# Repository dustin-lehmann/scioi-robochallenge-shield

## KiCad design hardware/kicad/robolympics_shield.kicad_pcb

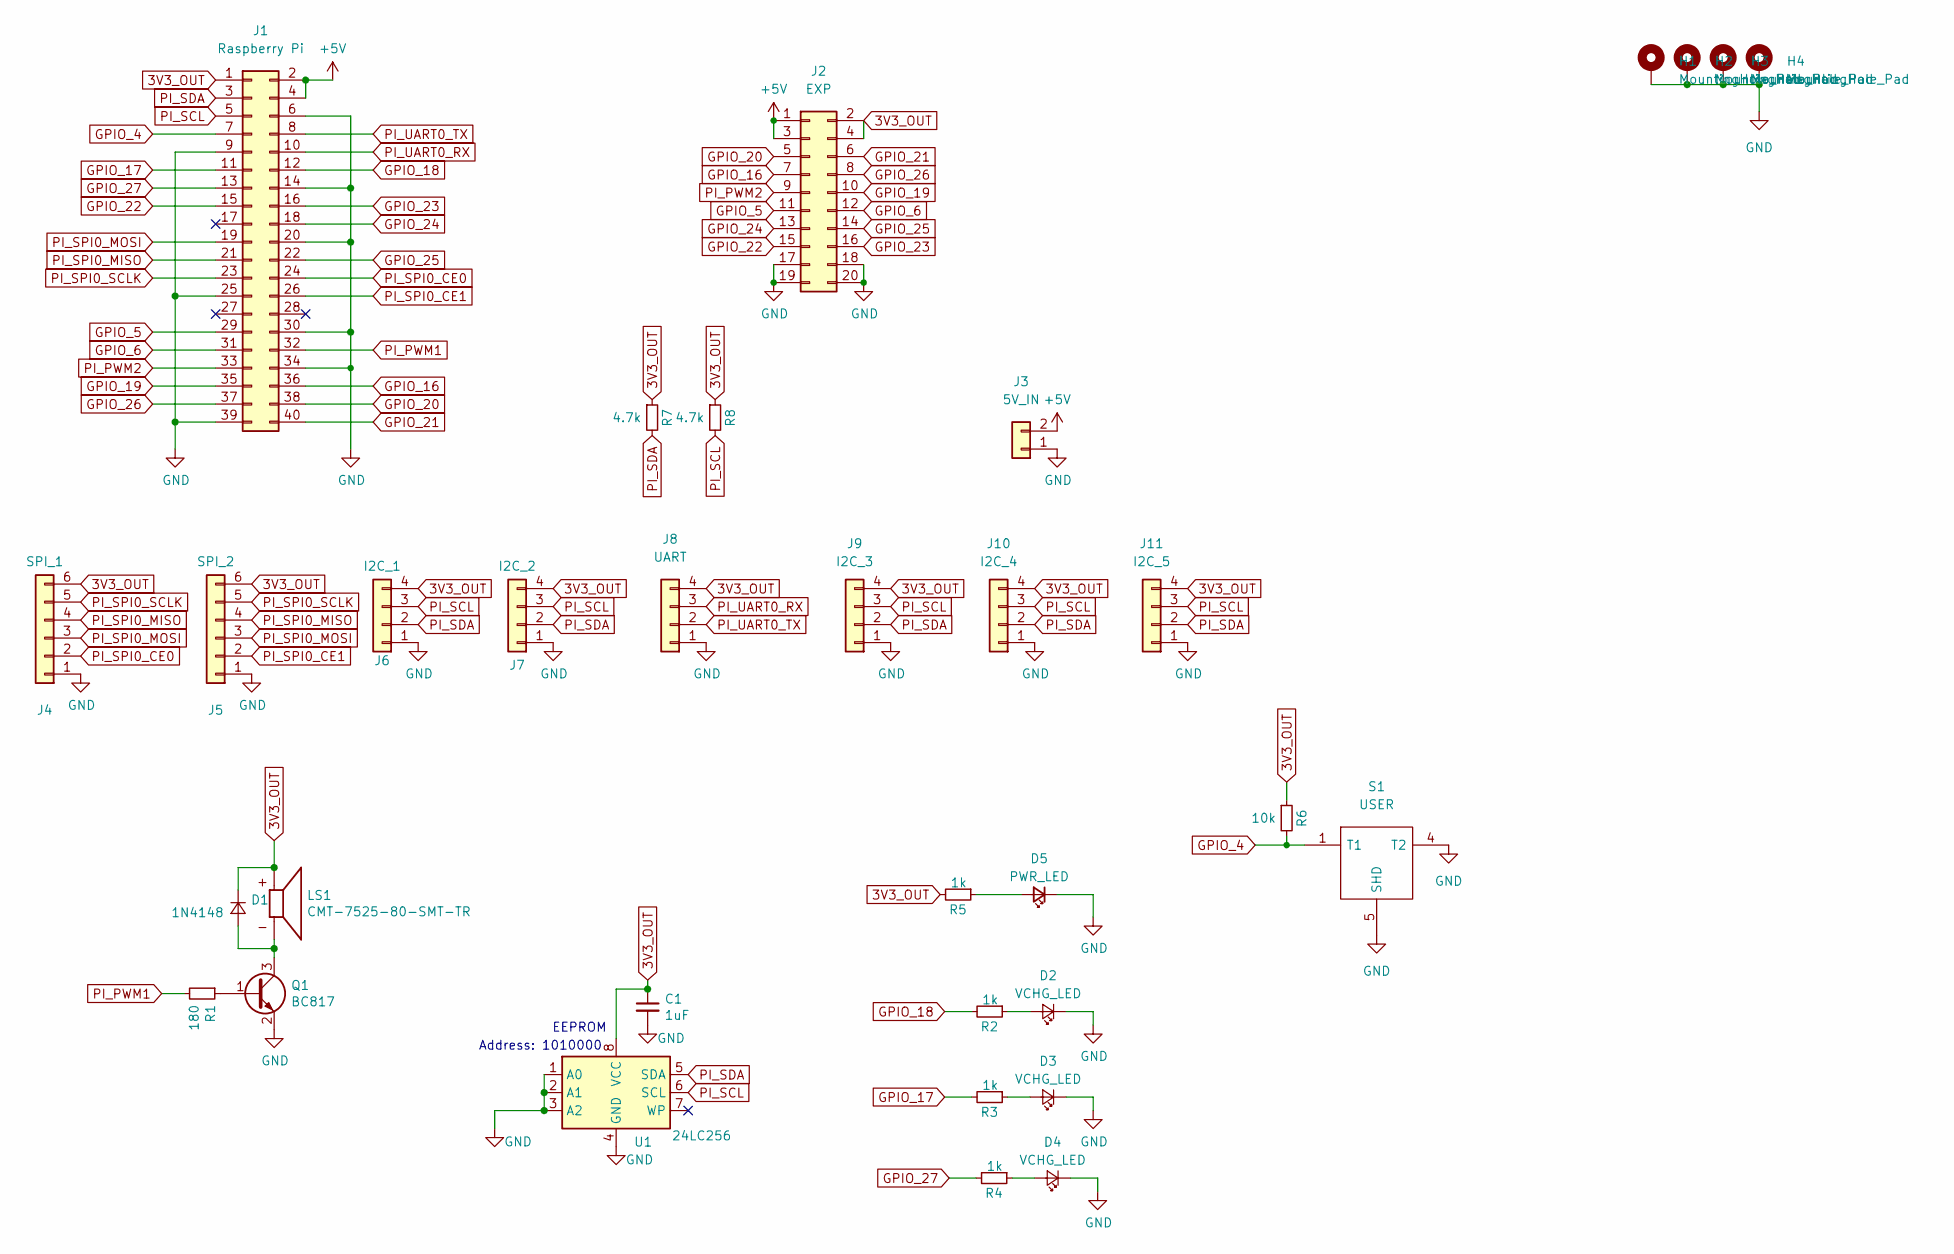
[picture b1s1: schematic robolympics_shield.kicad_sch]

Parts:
C1: 1uF; C_0805_2012Metric
D1: 1N4148; D_0805_2012Metric_Pad1.15x1.40mm_HandSolder
D2, D3, D4: VCHG_LED; LED_0402_1005Metric
D5: PWR_LED; LED_0603_1608Metric
H1, H2, H3, H4: MountingHole_Pad; MountingHole_2.7mm_M2.5_DIN965
J1: Raspberry Pi; PinSocket_2x20_P2.54mm_Vertical
J2: EXP; PinHeader_2x10_P2.54mm_Vertical
J3: 5V_IN; SHDRRA2W82P0X350_1X2_900X920X745P
J4: SPI_1; Molex_KK-254_AE-6410-06A_1x06_P2.54mm_Vertical
J5: SPI_2; Molex_KK-254_AE-6410-06A_1x06_P2.54mm_Vertical
J6: I2C_1; Molex_KK-254_AE-6410-04A_1x04_P2.54mm_Vertical
J7: I2C_2; Molex_KK-254_AE-6410-04A_1x04_P2.54mm_Vertical
J8: UART; Molex_KK-254_AE-6410-04A_1x04_P2.54mm_Vertical
J9: I2C_3; Molex_KK-254_AE-6410-04A_1x04_P2.54mm_Vertical
J10: I2C_4; Molex_KK-254_AE-6410-04A_1x04_P2.54mm_Vertical
J11: I2C_5; Molex_KK-254_AE-6410-04A_1x04_P2.54mm_Vertical
LS1: CMT-7525-80-SMT-TR; XDCR_CMT-7525-80-SMT-TR
Q1: BC817; SOT-23
R1: 180; R_0603_1608Metric
R2, R3, R4, R5: 1k; R_0603_1608Metric
R6: 10k; R_0603_1608Metric
R7, R8: 4.7k; R_0603_1608Metric
S1: USER; TL6330AF200Q; Mouser Part Number 612-TL6330AF200Q
U1: 24LC256; DFN-8-1EP_6x5mm_P1.27mm_EP2x2mm

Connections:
3V3_OUT: C1.1, D1.1 (K), J1.1, J2.2, J2.4, J4.6, J5.6, J6.4, J7.4, J8.4, J9.4, J10.4, J11.4, LS1.P, R5.2, R6.1, R7.1, R8.1, U1.8 (VCC)
+5V: J1.2, J1.4, J2.1, J2.3, J3.2
GND: C1.2, D2.1 (K), D3.1 (K), D4.1 (K), D5.1 (K), H1.1, H2.1, H3.1, H4.1, J1.6, J1.9, J1.14, J1.20, J1.25, J1.30, J1.34, J1.39, J2.17, J2.18, J2.19, J2.20, J3.1, J4.1, J5.1, J6.1, J7.1, J8.1, J9.1, J10.1, J11.1, Q1.2 (E), S1.3, S1.4 (T2), S1.5 (SHD), U1.1 (A0), U1.2 (A1), U1.3 (A2), U1.4 (GND)
GPIO_4: J1.7, R6.2, S1.1 (T1), S1.2
GPIO_5: J1.29, J2.11
GPIO_6: J1.31, J2.12
GPIO_16: J1.36, J2.7
GPIO_17: J1.11, R3.2
GPIO_18: J1.12, R2.2
GPIO_19: J1.35, J2.10
GPIO_20: J1.38, J2.5
GPIO_21: J1.40, J2.6
GPIO_22: J1.15, J2.15
GPIO_23: J1.16, J2.16
GPIO_24: J1.18, J2.13
GPIO_25: J1.22, J2.14
GPIO_26: J1.37, J2.8
GPIO_27: J1.13, R4.2
unnamed: D1.2 (A), LS1.N, Q1.3 (C)
unnamed: D2.2 (A), R2.1
unnamed: D3.2 (A), R3.1
unnamed: D4.2 (A), R4.1
unnamed: D5.2 (A), R5.1
unnamed: Q1.1 (B), R1.1
PI_PWM1: J1.32, R1.2
PI_PWM2: J1.33, J2.9
PI_SCL: J1.5, J6.3, J7.3, J9.3, J10.3, J11.3, R8.2, U1.6 (SCL)
PI_SDA: J1.3, J6.2, J7.2, J9.2, J10.2, J11.2, R7.2, U1.5 (SDA)
PI_SPI0_CE0: J1.24, J4.2
PI_SPI0_CE1: J1.26, J5.2
PI_SPI0_MISO: J1.21, J4.4, J5.4
PI_SPI0_MOSI: J1.19, J4.3, J5.3
PI_SPI0_SCLK: J1.23, J4.5, J5.5
PI_UART0_RX: J1.10, J8.3
PI_UART0_TX: J1.8, J8.2

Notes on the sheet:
Address: 1010000
EEPROM

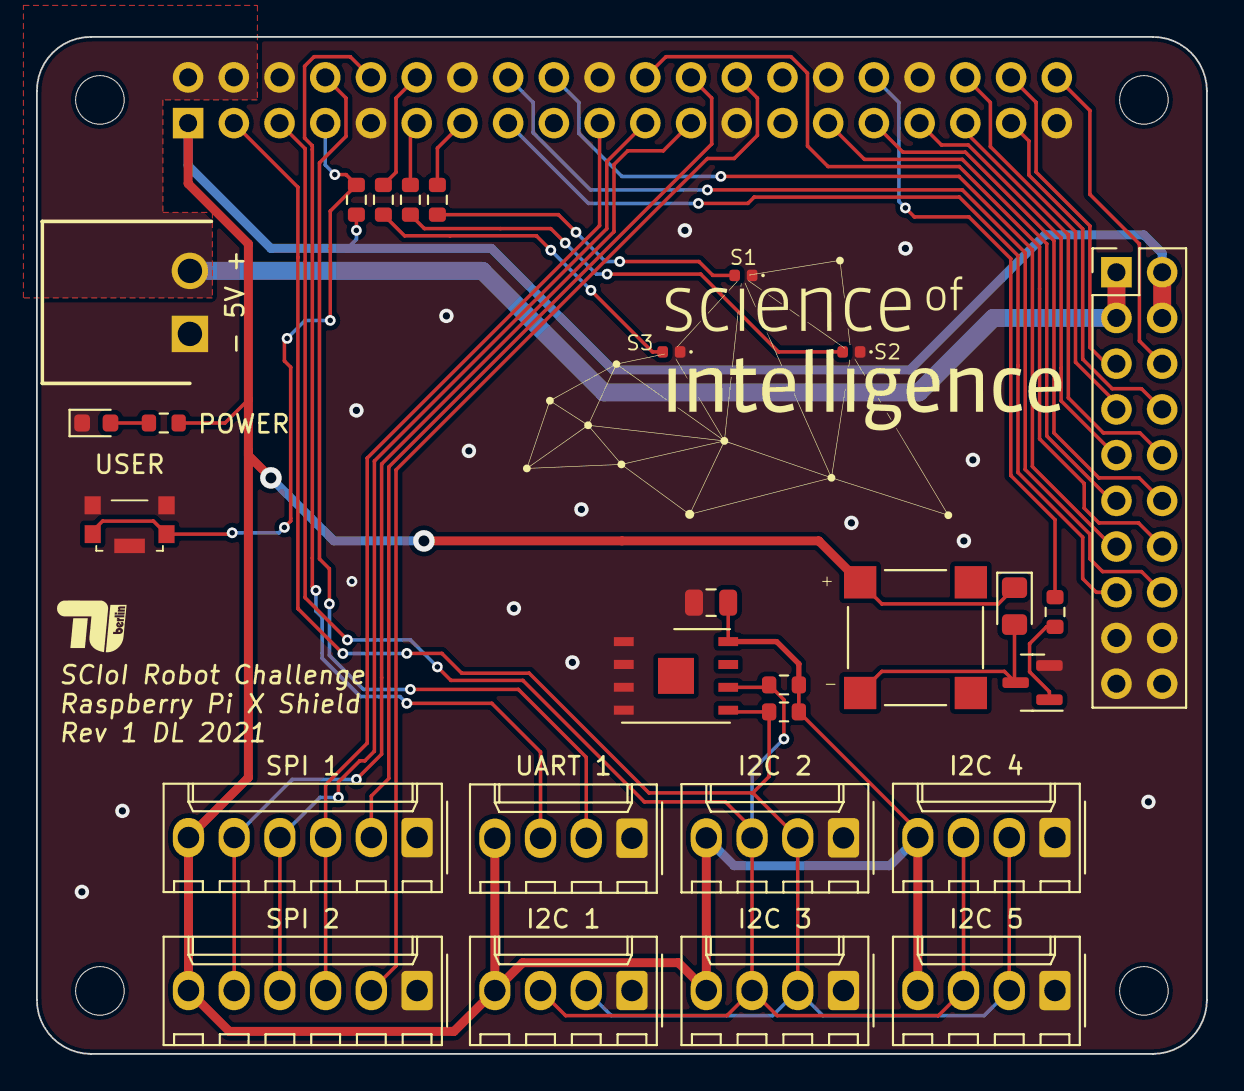
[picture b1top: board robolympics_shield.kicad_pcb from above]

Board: 2 copper layers, 65.0 x 56.5 mm, 33 parts (1 on the bottom side), 35 nets.
